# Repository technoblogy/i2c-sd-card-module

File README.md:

# I2C SD-Card Module

An SD-card module based on an ATtiny1614 that allows you to write to and read from files on an SD card using a two-wire I2C interface.

For more information see [I2C SD-Card Module](http://www.technoblogy.com/show?3XEP).

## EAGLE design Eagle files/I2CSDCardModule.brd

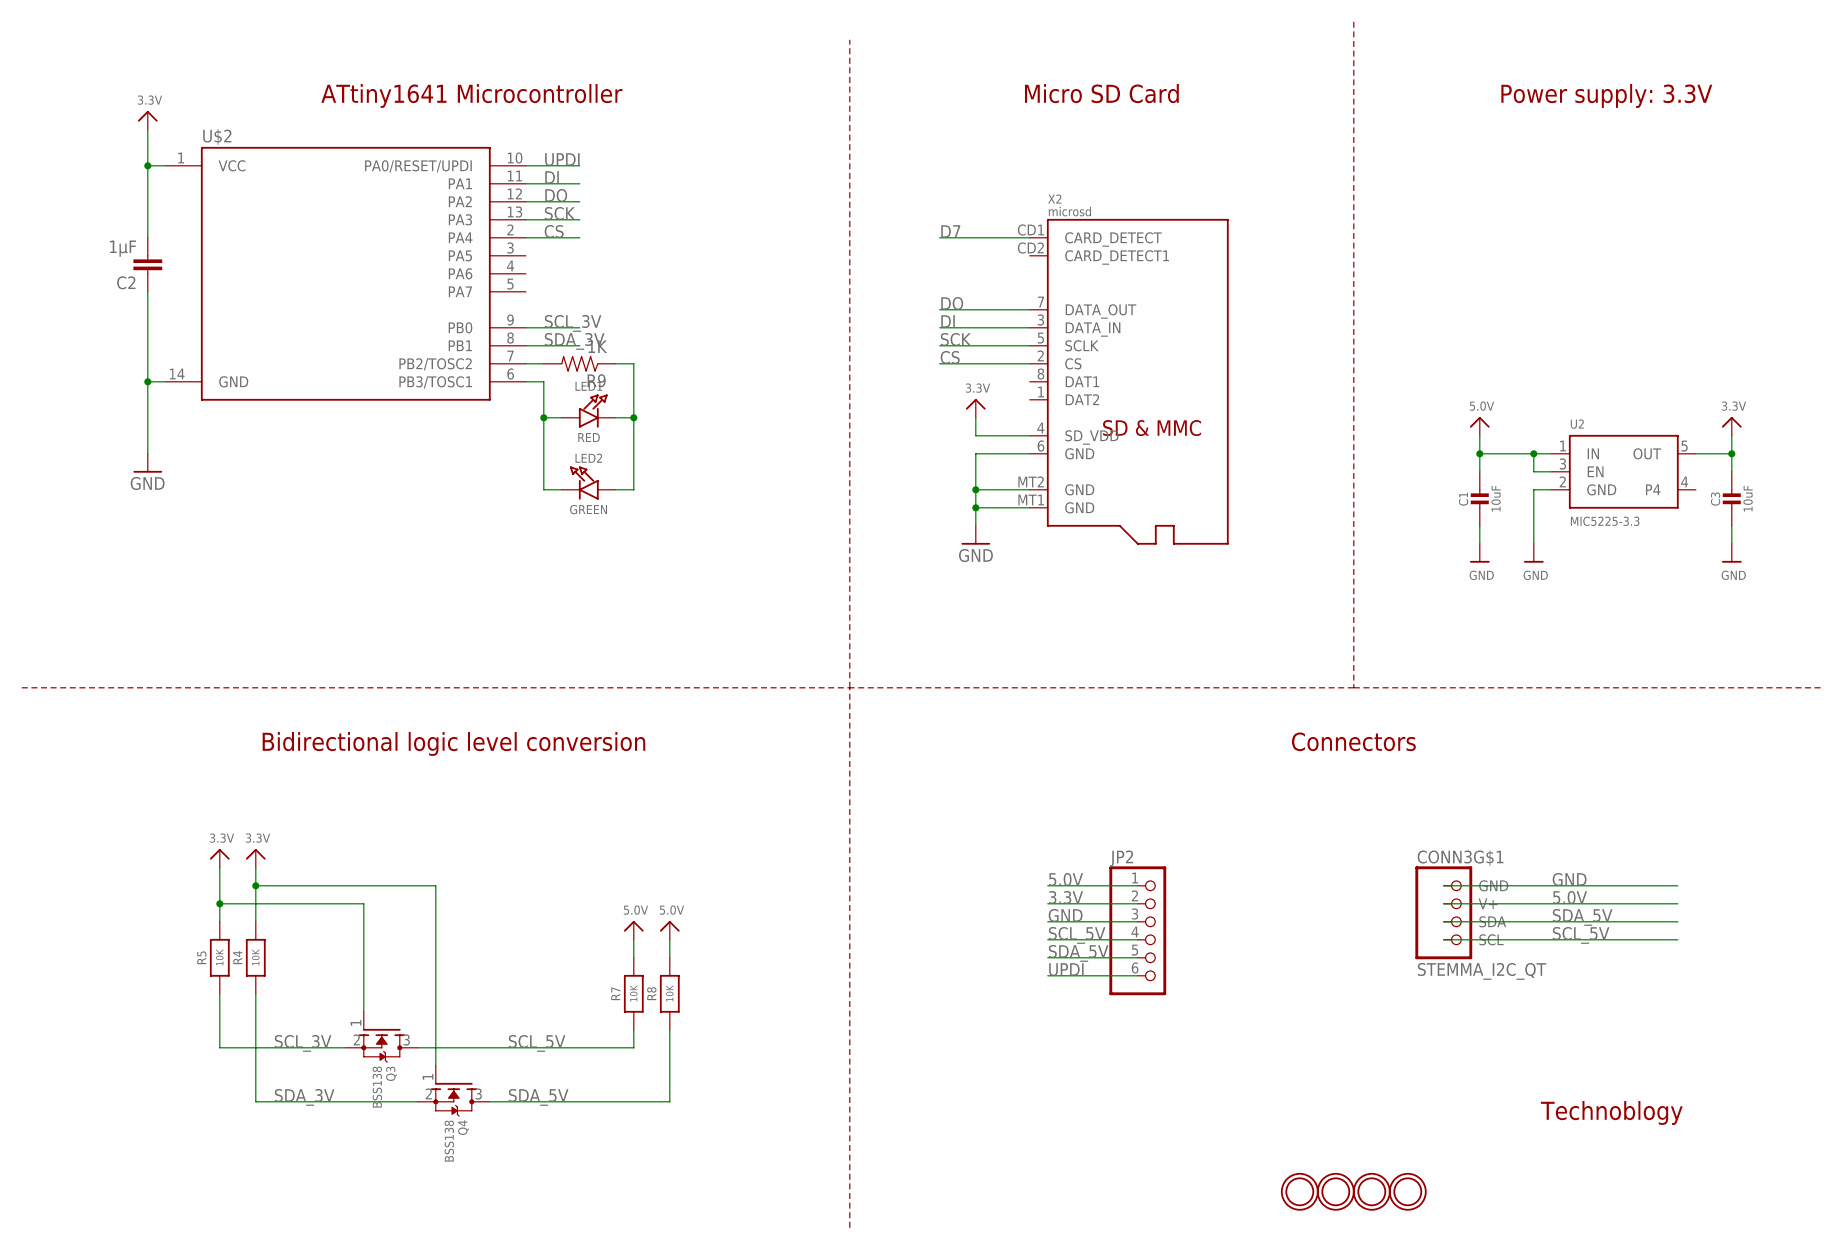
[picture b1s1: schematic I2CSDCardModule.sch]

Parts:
C1, C3: 10uF; 0805-NO
C2: 1µF; 0805
CONN3: STEMMA_I2C_QT; JST_SH4
JP2: HEADER-1X6ROUND; 1X06_ROUND
LED1: RED; CHIPLED_0805_NOOUTLINE
LED2: GREEN; CHIPLED_0805_NOOUTLINE
Q3, Q4: BSS138; SOT23-WIDE
R4, R5, R7, R8: 10K; 0805-NO
R9: 1K; 0805
U2: MIC5225-3.3; SOT23-5
U$1, U$5, U$6, U$9: MOUNTINGHOLE2.5; MOUNTINGHOLE_2.5_PLATED
U$2: ATTINY414; SO14
X2: microsd; MICROSD

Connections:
3.3V: C2.2, C3.1, JP2.2, Q3.1 (G), Q4.1 (G), R4.2, R5.2, U2.5 (OUT), U$2.1 (VCC), X2.4 (SD_VDD)
5.0V: C1.1, CONN3.2 (V+), JP2.1, R7.2, R8.2, U2.1 (IN), U2.3 (EN)
CS: U$2.2 (PA4), X2.2 (CS)
D7: X2.CD1 (CARD_DETECT)
DI: U$2.11 (PA1), X2.3 (DATA_IN)
DO: U$2.12 (PA2), X2.7 (DATA_OUT)
GND: C1.2, C2.1, C3.2, CONN3.1 (GND), JP2.3, U2.2 (GND), U$2.14 (GND), X2.6 (GND), X2.MT1 (GND), X2.MT2 (GND)
unnamed: LED1.A, LED2.C, U$2.6 (PB3/TOSC1)
unnamed: LED1.C, LED2.A, R9.1
unnamed: R9.2, U$2.7 (PB2/TOSC2)
SCK: U$2.13 (PA3), X2.5 (SCLK)
SCL_3V: Q3.2 (S), R5.1, U$2.9 (PB0)
SCL_5V: CONN3.4 (SCL), JP2.4, Q3.3 (D), R7.1
SDA_3V: Q4.2 (S), R4.1, U$2.8 (PB1)
SDA_5V: CONN3.3 (SDA), JP2.5, Q4.3 (D), R8.1
UPDI: JP2.6, U$2.10 (PA0/RESET/UPDI)

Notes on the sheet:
Power supply: 3.3V
ATtiny1641 Microcontroller
Technoblogy
Bidirectional logic level conversion
Micro SD Card
Connectors

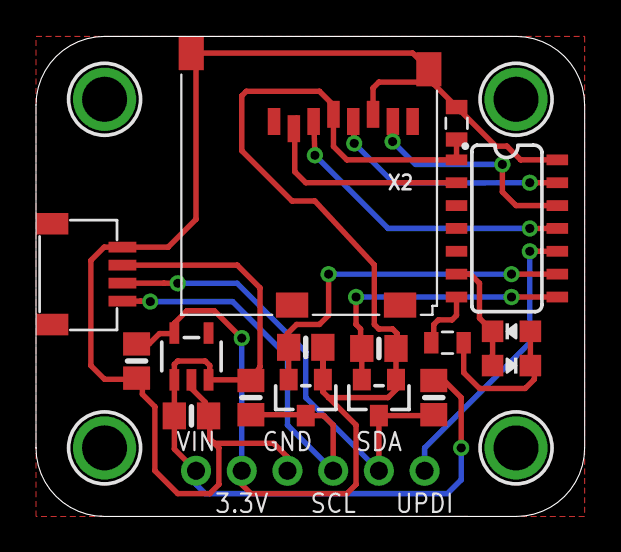
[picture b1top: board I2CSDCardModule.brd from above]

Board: 2 copper layers, 30.5 x 26.7 mm, 21 parts (0 on the bottom side), 15 nets.

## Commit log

2022-07-07 Version 1 - 7th July 2022
2022-07-08 Examples
2022-07-14 Eagle files
2025-04-07 Update I2CSDCardModule.ino
    Added function to retrieve if file exists
    New command "E" from host checks if file exists are returns 1 if the file or directory exists, 0 if not.
    Corrected compie warning in boolean DataHostWrite () by adding return false; to end of function
2025-04-17 Update I2CSDCardArduinoWire.ino
    Better memory management in the read file section
    also better handling of files larger than 32 bytes
2025-04-18 Update I2CSDCardArduinoWire.ino
    Added two new functions.
    1. function to check if a file exists on the SD card
    2. function to reset the ATtiny1614 from master via i2c
2025-04-18 Update I2CSDCardModule.ino
    Added function to retrieve if file exists
    Corrected Arduino compile warning (control reaches end of non-void function) in boolean DataHostWrite ()
    Added function to remove a file from the SD card.
    Changed general int to stdint.h types saving a few bytes in memory and storage
    Added software reset functioon so the ATTiny can be reset from another controler.
2025-04-18 Update I2CSDCardModule.ino
    fixed typo
2025-04-18 Update I2CSDCardModule.ino
    fixed i2c address to match I2CSDCardArduinoWire.ino
2025-04-19 Update I2CSDCardArduinoWire.ino
    Added ability to list SD card contents
2025-04-19 Update I2CSDCardModule.ino
    Pretty much re-wrote the whole module for better use of the ATtiny's architecture.
    -Added ability to list contents of SD Card
    -Added ability to create directories
    The optimizations include:
    1. Using a switch statement instead of multiple if-else conditions, which is more efficient for the ATtiny1614's architecture
    2. Consolidating the response into a single variable to reduce register usage
2025-04-19 Update I2CSDCardModule.ino
    changed i2c address back to 55 to match Arduino demo
2025-04-19 Update I2CSDCardArduinoWire.ino
    fixed typos
2025-04-19 Update I2CSDCardArduinoWire.ino
    Slight optimization of ChkFileExistsOnSD()
2025-04-22 Update I2CSDCardArduinoWire.ino
    Here’s a summary of the improvements made to your original I2CSDCardArduinoWire.ino firmware, along with notes on compatibility with other MCUs such as ESP8266, ESP32, and other common I2C master con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
    ## Summary of Improvements
    - **File Existence Check:**
    Added a function to check if a file exists on the SD card (`SD.exists(Filename)`).
    - **Compile Warning Fix:**
    Corrected a warning in `boolean DataHostWrite()` by ensuring all code paths return a value.
2025-04-22 Update I2CSDCardModule.ino
    Here’s a summary of the improvements made to your original I2CSDCardArduinoWire.ino firmware, along with notes on compatibility with other MCUs such as ESP8266, ESP32, and other common I2C master con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
    ## Summary of Improvements
    - **File Existence Check:**
    Added a function to check if a file exists on the SD card (`SD.exists(Filename)`).
    - **Compile Warning Fix:**
    Corrected a warning in `boolean DataHostWrite()` by ensuring all code paths return a value.
2025-04-22 Update I2CSDCardArduinoWire.ino
    Demo that shows all the new functions
2025-09-13 Added ESP32 compatibility demo
2026-03-10 CC BY-SA

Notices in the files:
parts and their libraries:
microbuilder: This work is placed in the public domain, and may be freely used for commercial and non-commercial work with the following conditions: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
SparkFun-Capacitors: Licensing: CC v3.0 Share-Alike You are welcome to use this library for commercial purposes.
